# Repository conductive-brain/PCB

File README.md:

# PCB

Printed circuit boards designed in KiCad. Each board has its own folder with its own README.

- **[ORX_Lite_Receiver](ORX_Lite_Receiver)**: a one-channel optical receiver on a 4-layer, 50 × 40 mm
  board. An S5971 photodiode, an OPA365 transimpedance amplifier and a Sallen-Key low-pass filter feed an
  ADS7042 12-bit, 1 MSPS ADC that sends its samples over SPI to a host board. Revision A is designed and
  its fabrication files are ready; it has not been ordered, built or tested yet.

License: MIT, see [LICENSE](LICENSE).

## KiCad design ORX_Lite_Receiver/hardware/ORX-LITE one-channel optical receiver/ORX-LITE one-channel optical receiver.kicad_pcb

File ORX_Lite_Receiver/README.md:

# ORX-LITE: one-channel optical receiver

A 4-layer board that measures light. A photodiode turns light into a small current, two op amps
turn the current into a clean voltage, and a 12-bit ADC sends it as numbers, 1 million per second,
over SPI to a 3.3 V microcontroller board (for example a Raspberry Pi Pico).

```
light → S5971 photodiode → OPA365 TIA (current to voltage) → OPA365 low-pass filter
      → 22 Ω + 1.5 nF → ADS7042 ADC (12 bit, 1 MSPS) → 2x5 header → microcontroller
```

Power comes from the microcontroller board: 5 V and 3.3 V through the header.

I drew this board by hand in KiCad 9, one step at a time. Each step is one commit, and each
commit message says what was added and why.

**Status:** revision A is designed and its fabrication files are ready. It has not been ordered,
built or tested yet.

## Files

```
docs/components.md       every part: what it is, why, how it is connected, where it came from
docs/design_process.md   the whole design: needs, formulas, values, reasoning
docs/figures/            simulation plots
calc/design_calcs.py     every number in design_process.md (writes calc/results.txt)
hardware/                the KiCad project
ORX_LITE_sim/            the SPICE simulation of the front end (KiCad 9, ngspice)
release/rev-A/           files to make revision A: Gerbers and drill files (gerbers/), parts
                         list and placement file (assembly/), schematic PDF, assembly
                         drawing and 3D picture (docs/), fabrication notes (README.md)
```

## Steps

| Step | What | State |
|---|---|---|
| 1 | KiCad project, page setup | done |
| 2 | power section: J1, ferrite beads, regulators U1 and U2, LED, test points TP1 to TP5 | done |
| 3 | front end, photodiode to filter: bias, TIA and its reference, Sallen-Key low-pass, ADC input RC | done |
| 4 | ADC and host connector: ADS7042, SPI resistors, mounting holes | done |
| 5 | footprints, ERC, netlist check, SPICE simulation | done |
| 6 | 4-layer board setup: outline, stackup, rules | done |
| 7 | placement | done |
| 8 | routing, ground and power planes, DRC | done |
| 9 | release files: Gerbers, drill files, parts list, placement file, documents, fabrication notes | done |

## Run the calculations

From this folder:

```
python calc/design_calcs.py   # writes calc/results.txt
```

Needs Python with numpy.

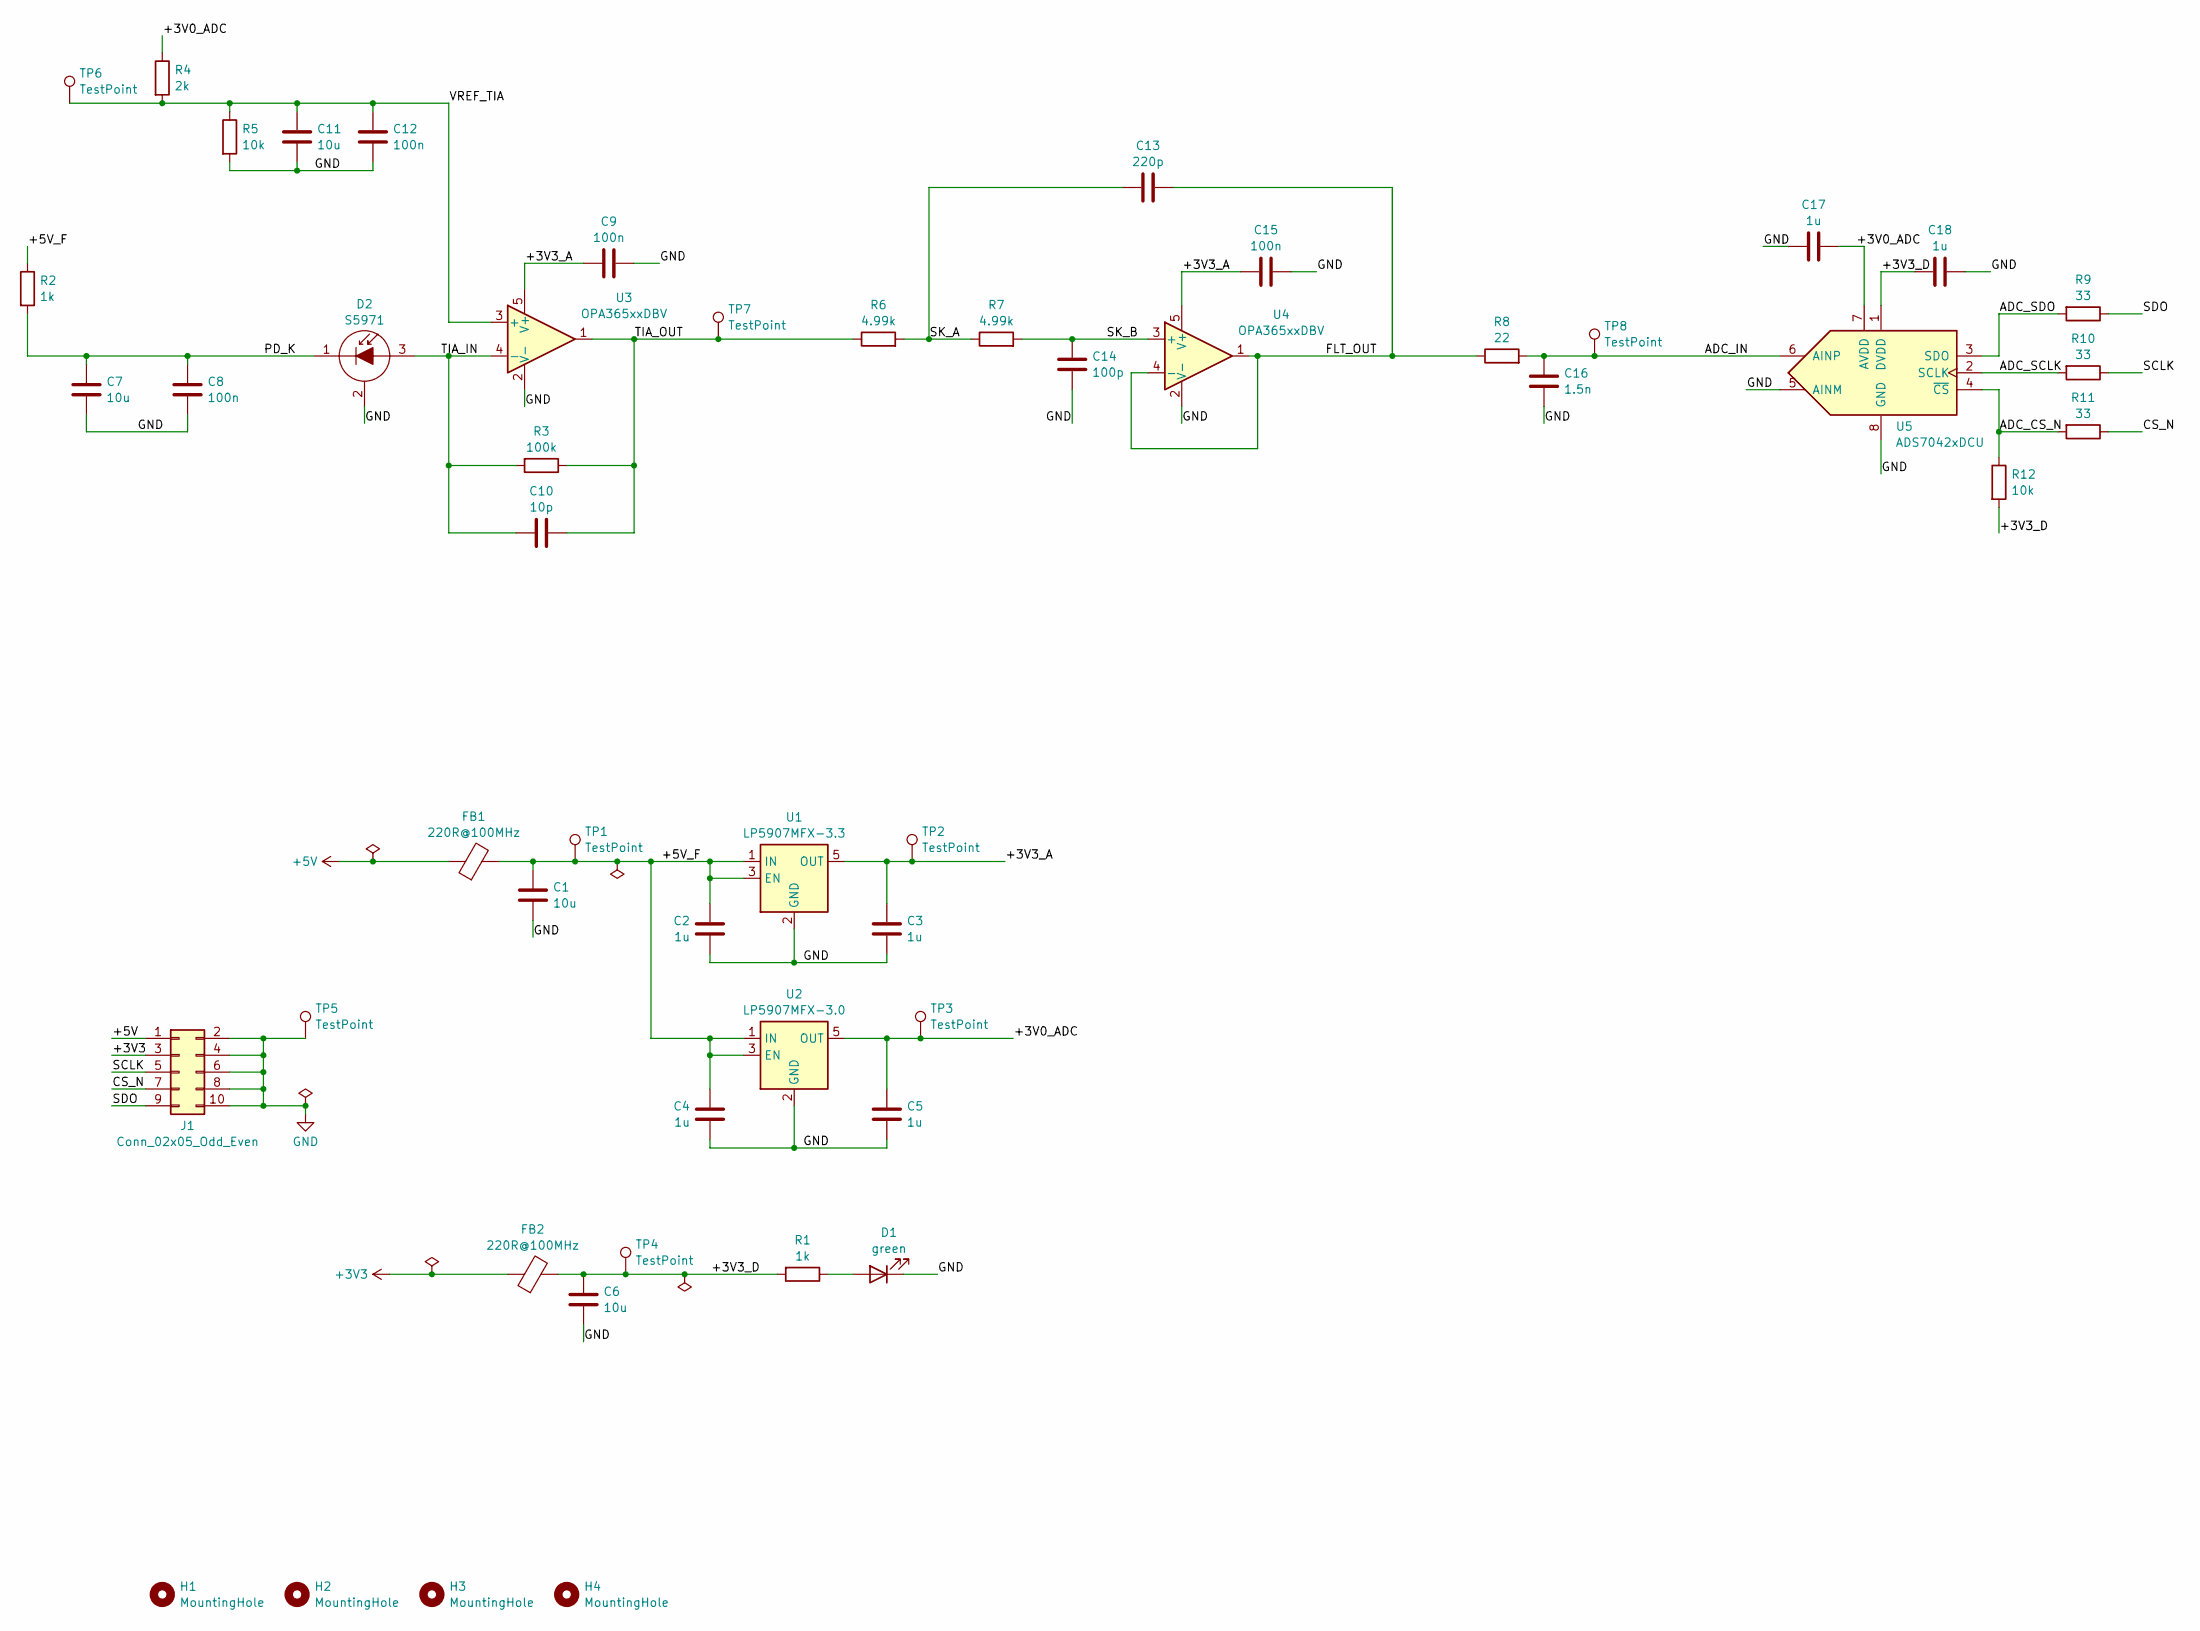
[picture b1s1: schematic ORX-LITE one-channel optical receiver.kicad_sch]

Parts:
C1, C6, C7, C11: 10u; C_0805_2012Metric
C2, C3, C4, C5, C17, C18: 1u; C_0603_1608Metric
C8, C9, C12, C15: 100n; C_0603_1608Metric
C10: 10p; C_0603_1608Metric
C13: 220p; C_0603_1608Metric
C14: 100p; C_0603_1608Metric
C16: 1.5n; C_0603_1608Metric
D1: green; LED_0603_1608Metric
D2: S5971; TO-18-3
FB1, FB2: 220R@100MHz; L_0603_1608Metric
H1, H2, H3, H4: MountingHole; MountingHole_3.2mm_M3
J1: Conn_02x05_Odd_Even; PinHeader_2x05_P2.54mm_Vertical
R1, R2: 1k; R_0603_1608Metric
R3: 100k; R_0603_1608Metric
R4: 2k; R_0603_1608Metric
R5, R12: 10k; R_0603_1608Metric
R6, R7: 4.99k; R_0603_1608Metric
R8: 22; R_0603_1608Metric
R9, R10, R11: 33; R_0603_1608Metric
TP1, TP2, TP3, TP4, TP5, TP6, TP7, TP8: TestPoint; TestPoint_Pad_D1.0mm
U1: LP5907MFX-3.3; SOT-23-5
U2: LP5907MFX-3.0; SOT-23-5
U3, U4: OPA365xxDBV; SOT-23-5
U5: ADS7042xDCU; VSSOP-8_2.3x2mm_P0.5mm

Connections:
+3V3: FB2.1, J1.3
+5V: FB1.1, J1.1
/+3V0_ADC: C5.1, C17.2, R4.1, TP3.1, U2.5 (OUT), U5.7 (AVDD)
/+3V3_A: C3.1, C9.1, C15.1, TP2.1, U1.5 (OUT), U3.5 (V+), U4.5 (V+)
/+3V3_D: C6.1, C18.2, FB2.2, R1.2, R12.2, TP4.1, U5.1 (DVDD)
/+5V_F: C1.1, C2.1, C4.1, FB1.2, R2.1, TP1.1, U1.1 (IN), U1.3 (EN), U2.1 (IN), U2.3 (EN)
/ADC_CS_N: R11.2, R12.1, U5.4 (~CS)
/ADC_IN: C16.1, R8.2, TP8.1, U5.6 (AINP)
/ADC_SCLK: R10.2, U5.2 (SCLK)
/ADC_SDO: R9.2, U5.3 (SDO)
/CS_N: J1.7, R11.1
/FLT_OUT: C13.1, R8.1, U4.1, U4.4 (-)
/PD_K: C7.1, C8.1, D2.1 (K), R2.2
/SCLK: J1.5, R10.1
/SDO: J1.9, R9.1
/SK_A: C13.2, R6.2, R7.1
/SK_B: C14.2, R7.2, U4.3 (+)
/TIA_IN: C10.2, D2.3 (A), R3.2, U3.4 (-)
/TIA_OUT: C10.1, R3.1, R6.1, TP7.1, U3.1
/VREF_TIA: C11.1, C12.1, R4.2, R5.1, TP6.1, U3.3 (+)
GND: C1.2, C2.2, C3.2, C4.2, C5.2, C6.2, C7.2, C8.2, C9.2, C11.2, C12.2, C14.1, C15.2, C16.2, C17.1, C18.1, D1.1 (K), D2.2 (C), J1.2, J1.4, J1.6, J1.8, J1.10, R5.2, TP5.1, U1.2 (GND), U2.2 (GND), U3.2 (V-), U4.2 (V-), U5.5 (AINM), U5.8 (GND)
unnamed: D1.2 (A), R1.1

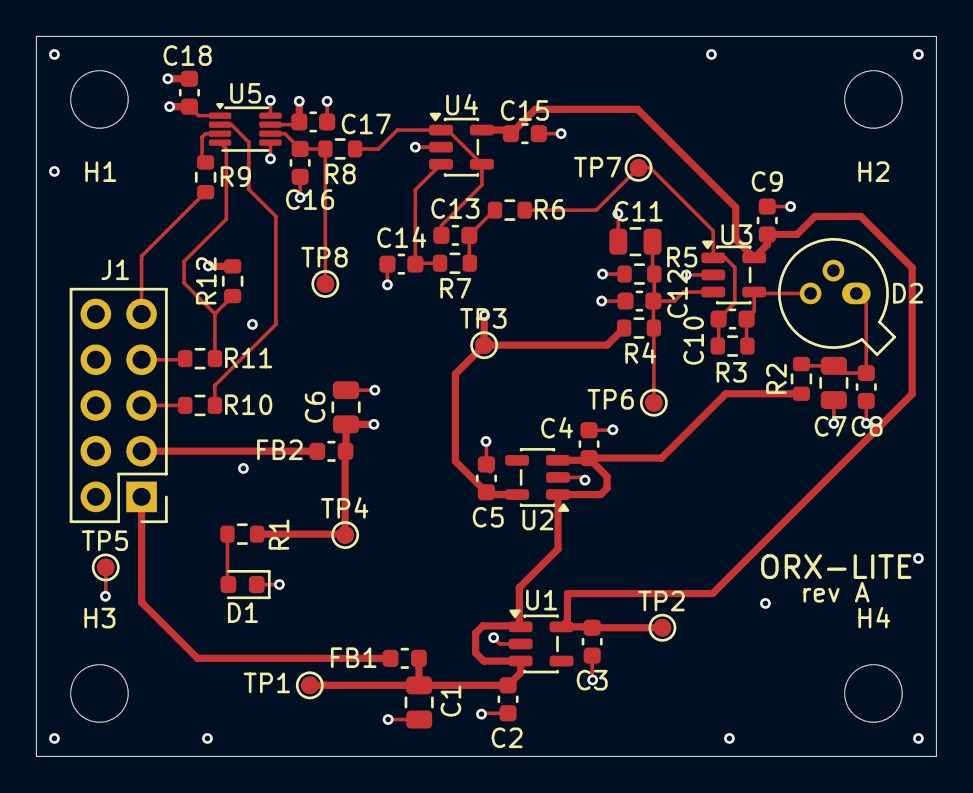
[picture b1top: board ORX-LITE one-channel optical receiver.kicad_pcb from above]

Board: 4 copper layers, 50.0 x 40.0 mm, 52 parts (0 on the bottom side), 22 nets.
